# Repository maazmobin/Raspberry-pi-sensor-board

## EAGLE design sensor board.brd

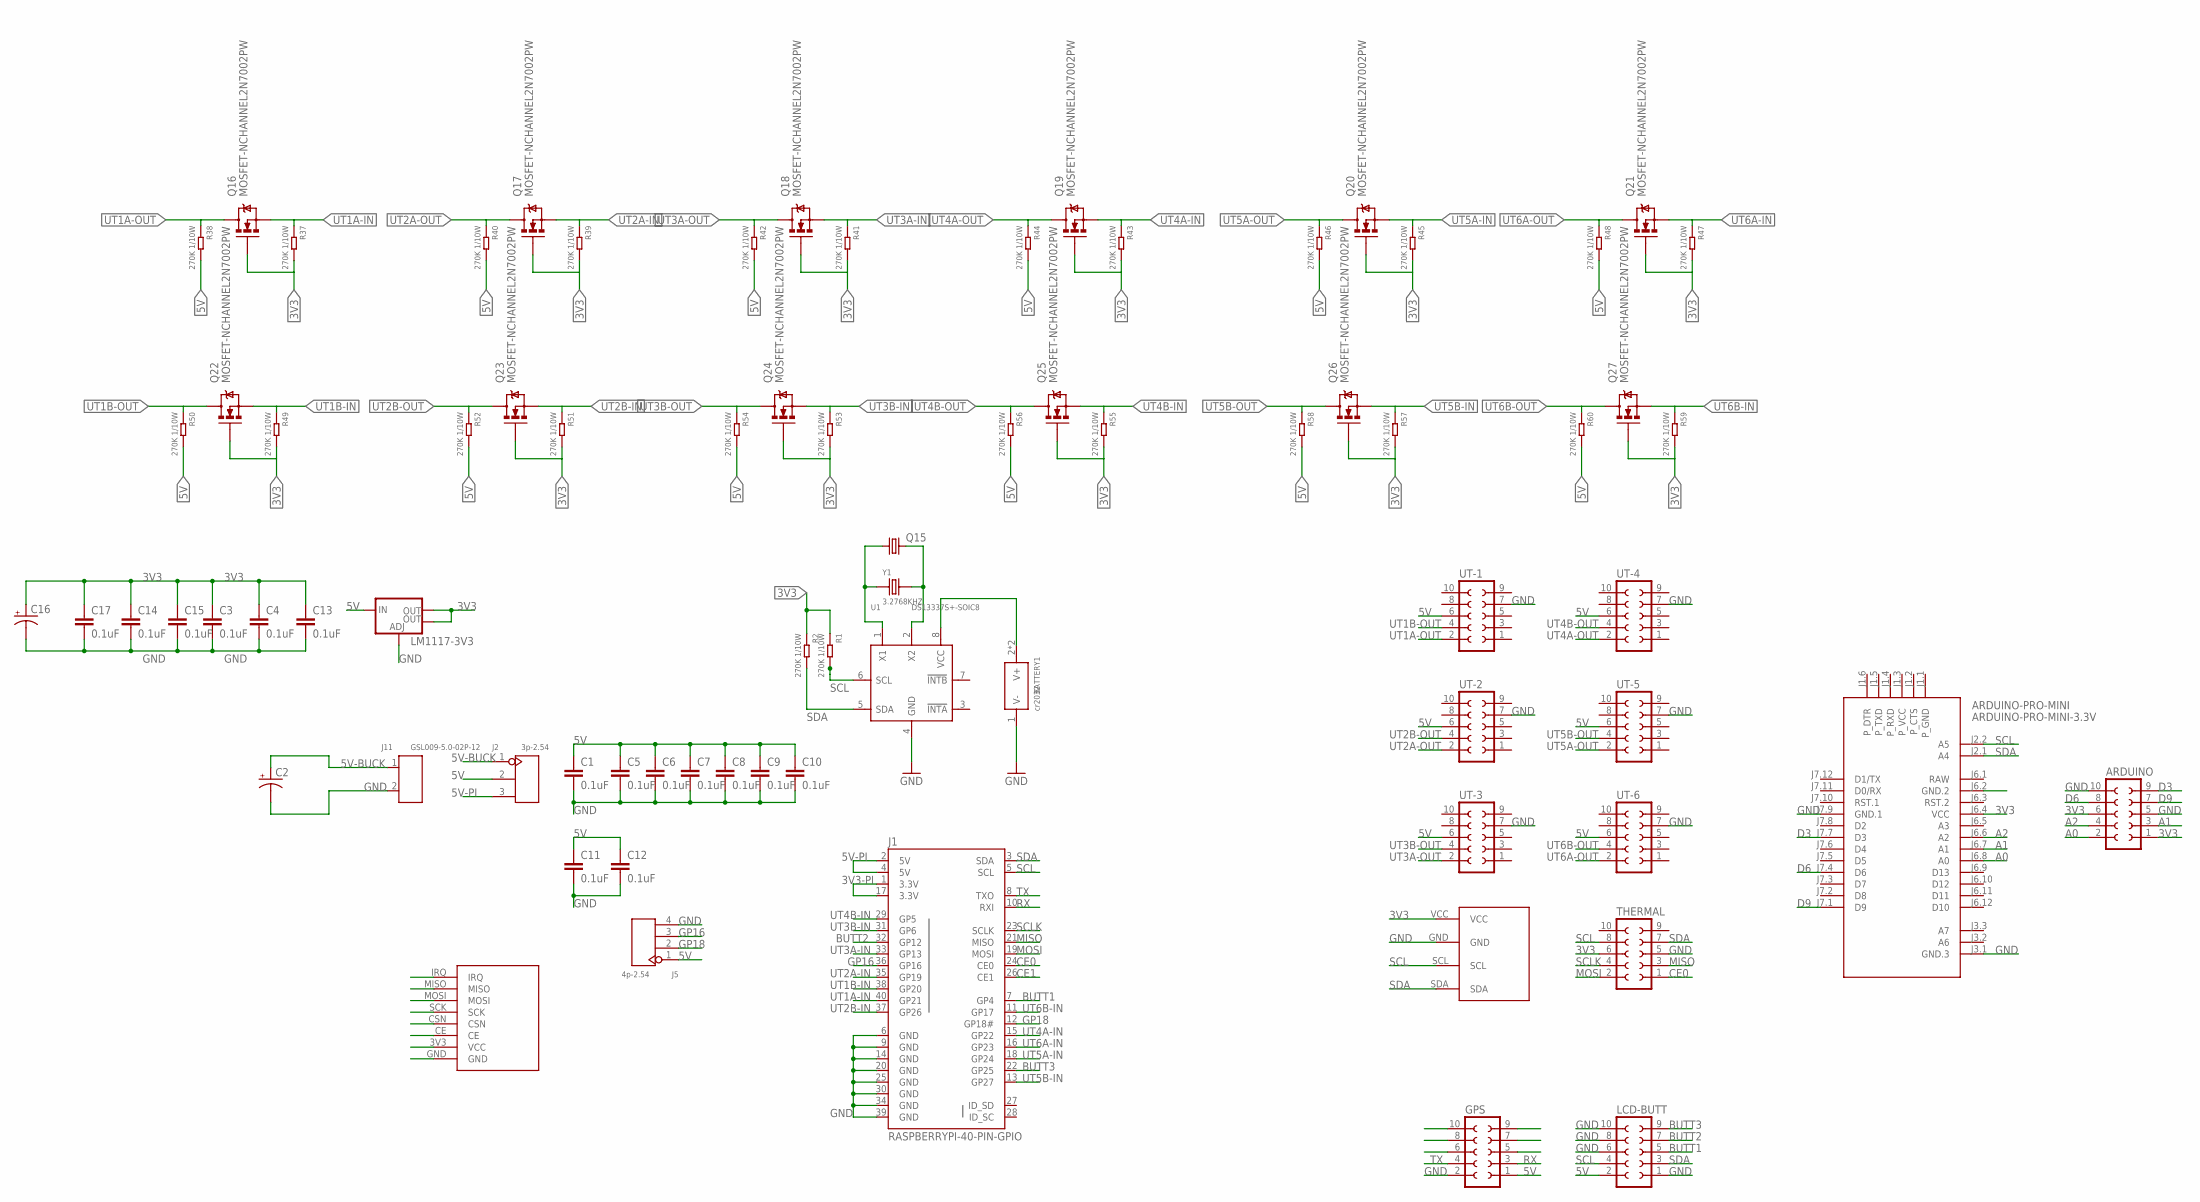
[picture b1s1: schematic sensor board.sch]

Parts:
ARDUINO: SOCKET-10V; S10V
ARDUINO-PRO-MINI: ARDUINO-PRO-MINI-3.3V; ARDUINO-PRO-MINI
BATTERY1: cr2032; BAT2P-20.32-CR2032
C1, C3, C4, C5, C6, C7, C8, C9, C10, C11, C12, C13, C14, C15, C17: 0.1uF; 0603-CAP
C2, C16: 100UF-25V-20%(PTH); CPOL-RADIAL-100UF-25V
GPS: SOCKET-10V; S10V
J1: RASPBERRYPI-40-PIN-GPIO; 2X20-SHROUDED
J2: 3p-2.54; H3-2.54
J5: 4p-2.54; H4-2.54
J11: GSL009-5.0-02P-12; H2-5.0-10.5X8.0MM
LCD-BUTT: SOCKET-10V; S10V
LM1117-3V3: V_REG_LM1117SOT223; SOT223
Q15: CRYSTALTC26H; TC26H
Q16, Q17, Q18, Q19, Q20, Q21, Q22, Q23, Q24, Q25, Q26, Q27: MOSFET-NCHANNEL2N7002PW; SOT323
R1, R2, R37, R38, R39, R40, R41, R42, R43, R44, R45, R46, R47, R48, R49, R50, R51, R52, R53, R54, R55, R56, R57, R58, R59, R60: 270K 1/10W; R0603
THERMAL: SOCKET-10V; S10V
U1: DS13337S+-SOIC8; SOIC8-1.27-5X4MM
U$1: IMU
U$2: NRF24L01+
UT-1, UT-2, UT-3, UT-4, UT-5, UT-6: SOCKET-10V; S10V
Y1: 3.2768KHZ; X2-SMD-L2.0X1.2X0.55MM

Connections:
3V3: ARDUINO.1, ARDUINO.6, ARDUINO-PRO-MINI.J6.4 (VCC), C3.1, C4.1, C13.1, C14.1, C15.1, C16.1 (+), C17.1, LM1117-3V3.2 (OUT), LM1117-3V3.4 (OUT), Q16.1 (G), Q17.1 (G), Q18.1 (G), Q19.1 (G), Q20.1 (G), Q21.1 (G), Q22.1 (G), Q23.1 (G), Q24.1 (G), Q25.1 (G), Q26.1 (G), Q27.1 (G), R1.1, R2.1, R37.2, R39.2, R41.2, R43.2, R45.2, R47.2, R49.2, R51.2, R53.2, R55.2, R57.2, R59.2, THERMAL.6, U$1.VCC, U$2.3V3 (VCC)
3V3-PI: J1.1 (3.3V), J1.17 (3.3V)
5V: C1.1, C5.1, C6.1, C7.1, C8.1, C9.1, C10.1, C11.1, C12.1, GPS.1, J2.2, J5.1, LCD-BUTT.2, LM1117-3V3.3 (IN), R38.2, R40.2, R42.2, R44.2, R46.2, R48.2, R50.2, R52.2, R54.2, R56.2, R58.2, R60.2, UT-1.6, UT-2.6, UT-3.6, UT-4.6, UT-5.6, UT-6.6
5V-BUCK: C2.1 (+), J2.1, J11.1
5V-PI: J1.2 (5V), J1.4 (5V), J2.3
A0: ARDUINO.2, ARDUINO-PRO-MINI.J6.8 (A0)
A1: ARDUINO.3, ARDUINO-PRO-MINI.J6.7 (A1)
A2: ARDUINO.4, ARDUINO-PRO-MINI.J6.6 (A2)
BUTT1: J1.7 (GP4), LCD-BUTT.5
BUTT2: J1.32 (GP12), LCD-BUTT.7
BUTT3: J1.22 (GP25), LCD-BUTT.9, U$2.CE
CE0: J1.24 (CE0), THERMAL.1
CE1: J1.26 (CE1), U$2.CSN
D3: ARDUINO.9, ARDUINO-PRO-MINI.J7.7 (D3)
D6: ARDUINO.8, ARDUINO-PRO-MINI.J7.4 (D6)
D9: ARDUINO.7, ARDUINO-PRO-MINI.J7.1 (D9)
GND: ARDUINO.5, ARDUINO.10, ARDUINO-PRO-MINI.J3.1 (GND.3), ARDUINO-PRO-MINI.J6.2 (GND.2), ARDUINO-PRO-MINI.J7.9 (GND.1), BATTERY1.1 (V-), C1.2, C2.2 (-), C3.2, C4.2, C5.2, C6.2, C7.2, C8.2, C9.2, C10.2, C11.2, C12.2, C13.2, C14.2, C15.2, C16.2 (-), C17.2, GPS.2, J1.6 (GND), J1.9 (GND), J1.14 (GND), J1.20 (GND), J1.25 (GND), J1.30 (GND), J1.34 (GND), J1.39 (GND), J5.4, J11.2, LCD-BUTT.1, LCD-BUTT.6, LCD-BUTT.8, LCD-BUTT.10, LM1117-3V3.1 (ADJ), THERMAL.5, U1.4 (GND), U$1.GND, U$2.GND, UT-1.7, UT-2.7, UT-3.7, UT-4.7, UT-5.7, UT-6.7
GP16: J1.36 (GP16), J5.3
GP18: J1.12 (GP18#), J5.2
MISO: J1.21 (MISO), THERMAL.3, U$2.MISO
MOSI: J1.19 (MOSI), THERMAL.2, U$2.MOSI
unnamed: BATTERY1.2 (V+), BATTERY1.3 (V+), U1.8 (VCC)
unnamed: Q15.1, U1.1 (X1), Y1.1
unnamed: Q15.2, U1.2 (X2), Y1.2
RAW: ARDUINO-PRO-MINI.J6.1 (RAW)
RX: GPS.3, J1.10 (RXI)
SCL: ARDUINO-PRO-MINI.J2.2 (A5), J1.5 (SCL), LCD-BUTT.4, R1.2, THERMAL.8, U1.6 (SCL), U$1.SCL
SCLK: J1.23 (SCLK), THERMAL.4, U$2.SCK
SDA: ARDUINO-PRO-MINI.J2.1 (A4), J1.3 (SDA), LCD-BUTT.3, R2.2, THERMAL.7, U1.5 (SDA), U$1.SDA
TX: GPS.4, J1.8 (TXO)
UT1A-IN: J1.40 (GP21), Q16.2 (S), R37.1
UT1A-OUT: Q16.3 (D), R38.1, UT-1.2
UT1B-IN: J1.38 (GP20), Q22.2 (S), R49.1
UT1B-OUT: Q22.3 (D), R50.1, UT-1.4
UT2A-IN: J1.35 (GP19), Q17.2 (S), R39.1
UT2A-OUT: Q17.3 (D), R40.1, UT-2.2
UT2B-IN: J1.37 (GP26), Q23.2 (S), R51.1
UT2B-OUT: Q23.3 (D), R52.1, UT-2.4
UT3A-IN: J1.33 (GP13), Q18.2 (S), R41.1
UT3A-OUT: Q18.3 (D), R42.1, UT-3.2
UT3B-IN: J1.31 (GP6), Q24.2 (S), R53.1
UT3B-OUT: Q24.3 (D), R54.1, UT-3.4
UT4A-IN: J1.15 (GP22), Q19.2 (S), R43.1
UT4A-OUT: Q19.3 (D), R44.1, UT-4.2
UT4B-IN: J1.29 (GP5), Q25.2 (S), R55.1
UT4B-OUT: Q25.3 (D), R56.1, UT-4.4
UT5A-IN: J1.18 (GP24), Q20.2 (S), R45.1
UT5A-OUT: Q20.3 (D), R46.1, UT-5.2
UT5B-IN: J1.13 (GP27), Q26.2 (S), R57.1
UT5B-OUT: Q26.3 (D), R58.1, UT-5.4
UT6A-IN: J1.16 (GP23), Q21.2 (S), R47.1
UT6A-OUT: Q21.3 (D), R48.1, UT-6.2
UT6B-IN: J1.11 (GP17), Q27.2 (S), R59.1
UT6B-OUT: Q27.3 (D), R60.1, UT-6.4

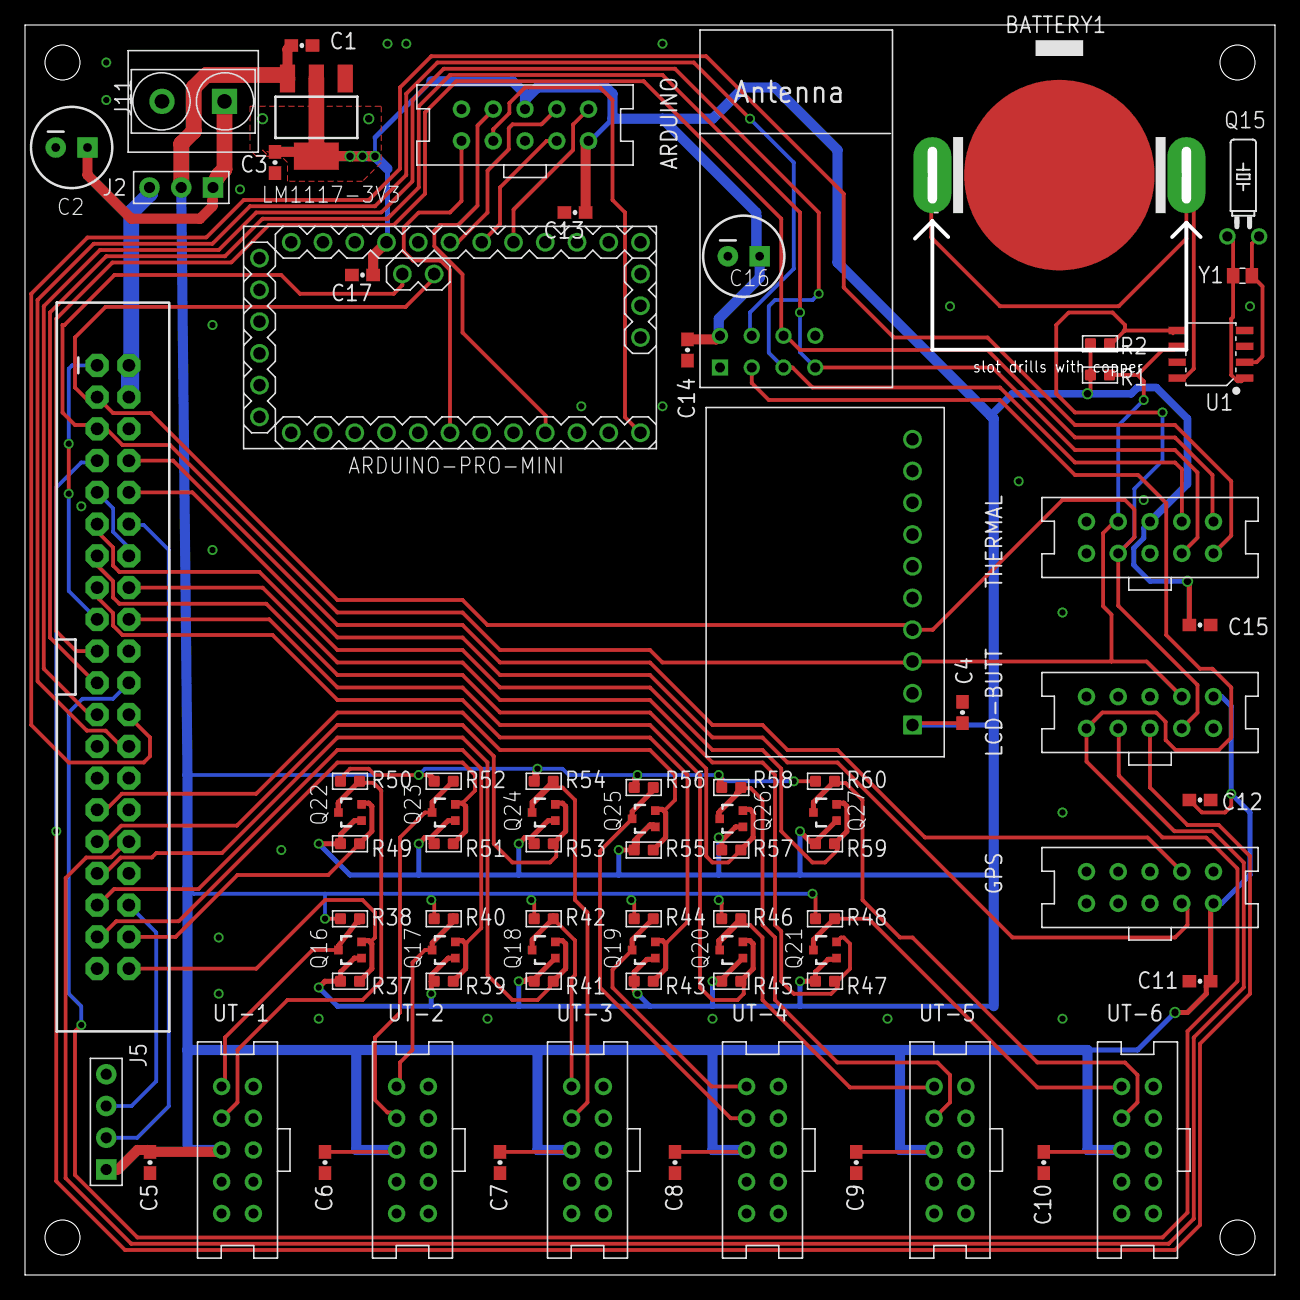
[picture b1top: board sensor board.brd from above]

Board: 2 copper layers, 100.0 x 100.0 mm, 77 parts (0 on the bottom side), 53 nets.

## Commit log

2017-08-02 :neckbeard: Added .gitattributes & .gitignore files
2017-08-02 doing schematic
2017-08-04 schematic conformation required
2017-08-06 aschmatic edit 1, overview Required
2017-08-07 On layout
2017-08-08 Review Required
2017-08-08 review 1

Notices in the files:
parts and their libraries:
SparkFun-Boards: Licensing: Creative Commons ShareAlike 4.0 International - https://creativecommons.org/licenses/by-sa/4.0
diy-modules: Released under the Creative Commons Attribution 4.0 International License: http://creativecommons.org/licenses/by/4.0
